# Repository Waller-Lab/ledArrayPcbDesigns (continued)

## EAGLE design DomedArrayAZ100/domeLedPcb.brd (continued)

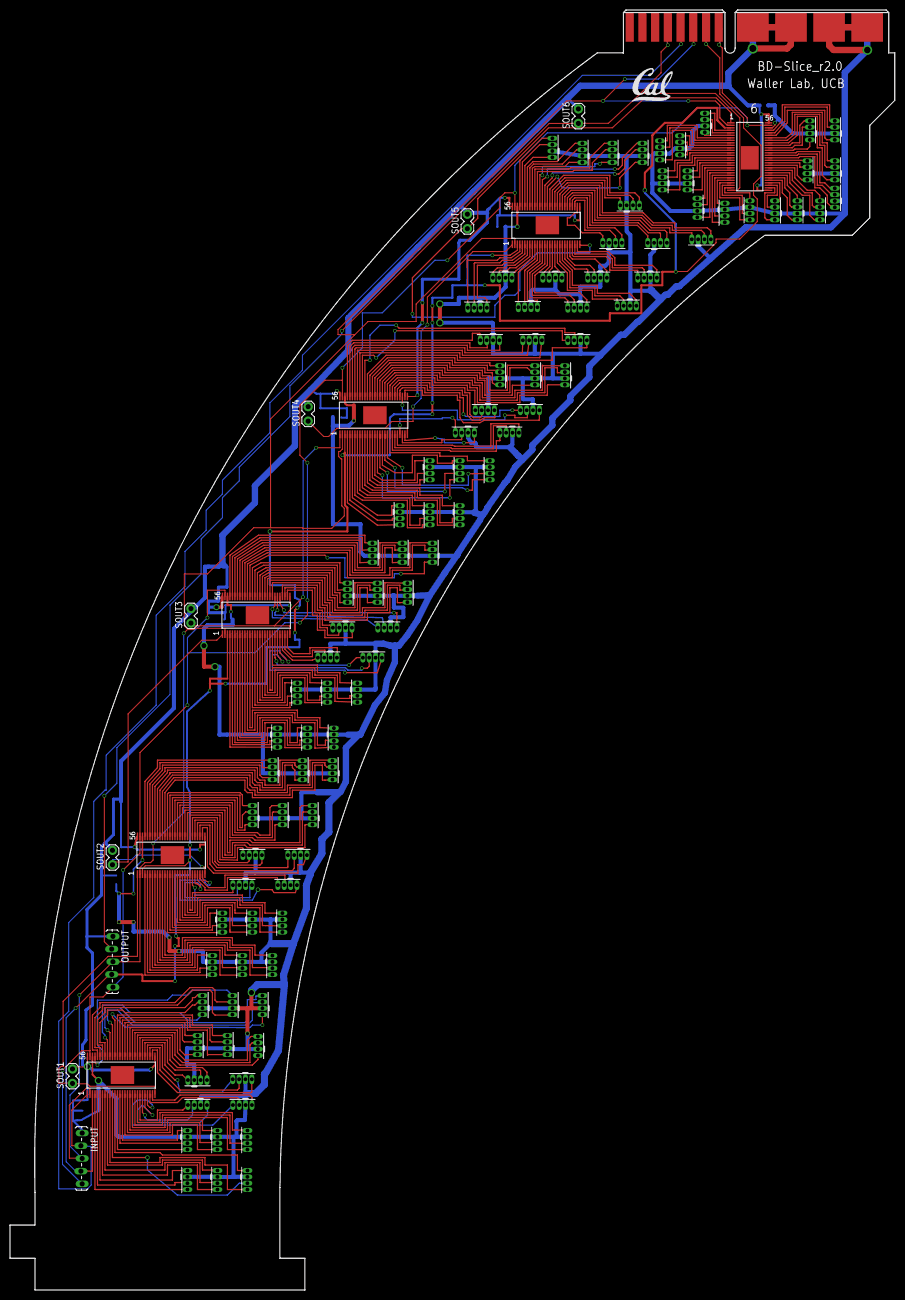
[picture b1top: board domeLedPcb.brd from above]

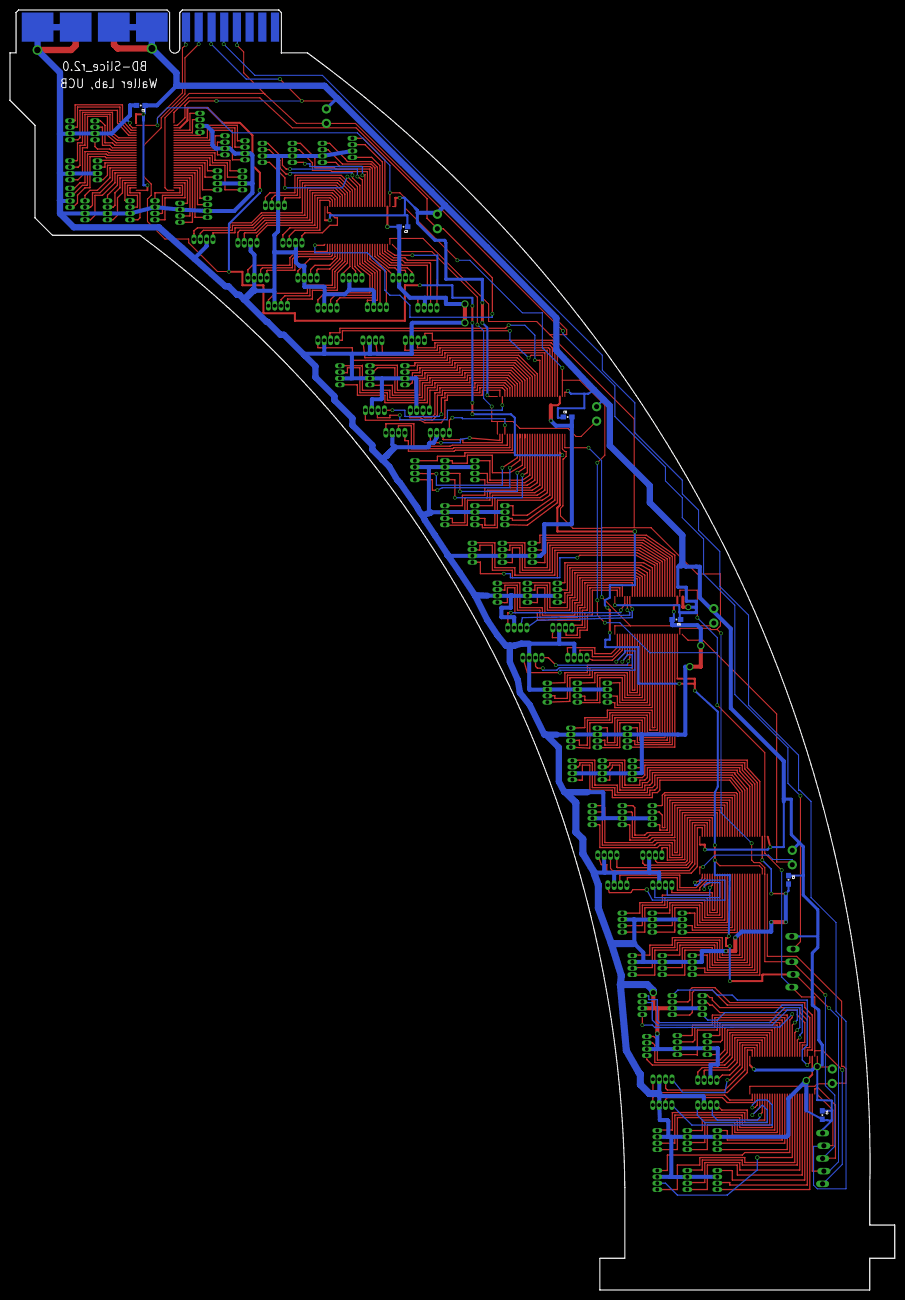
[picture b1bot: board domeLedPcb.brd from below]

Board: 2 copper layers, 177.0 x 256.1 mm, 117 parts (6 on the bottom side), 300 nets.

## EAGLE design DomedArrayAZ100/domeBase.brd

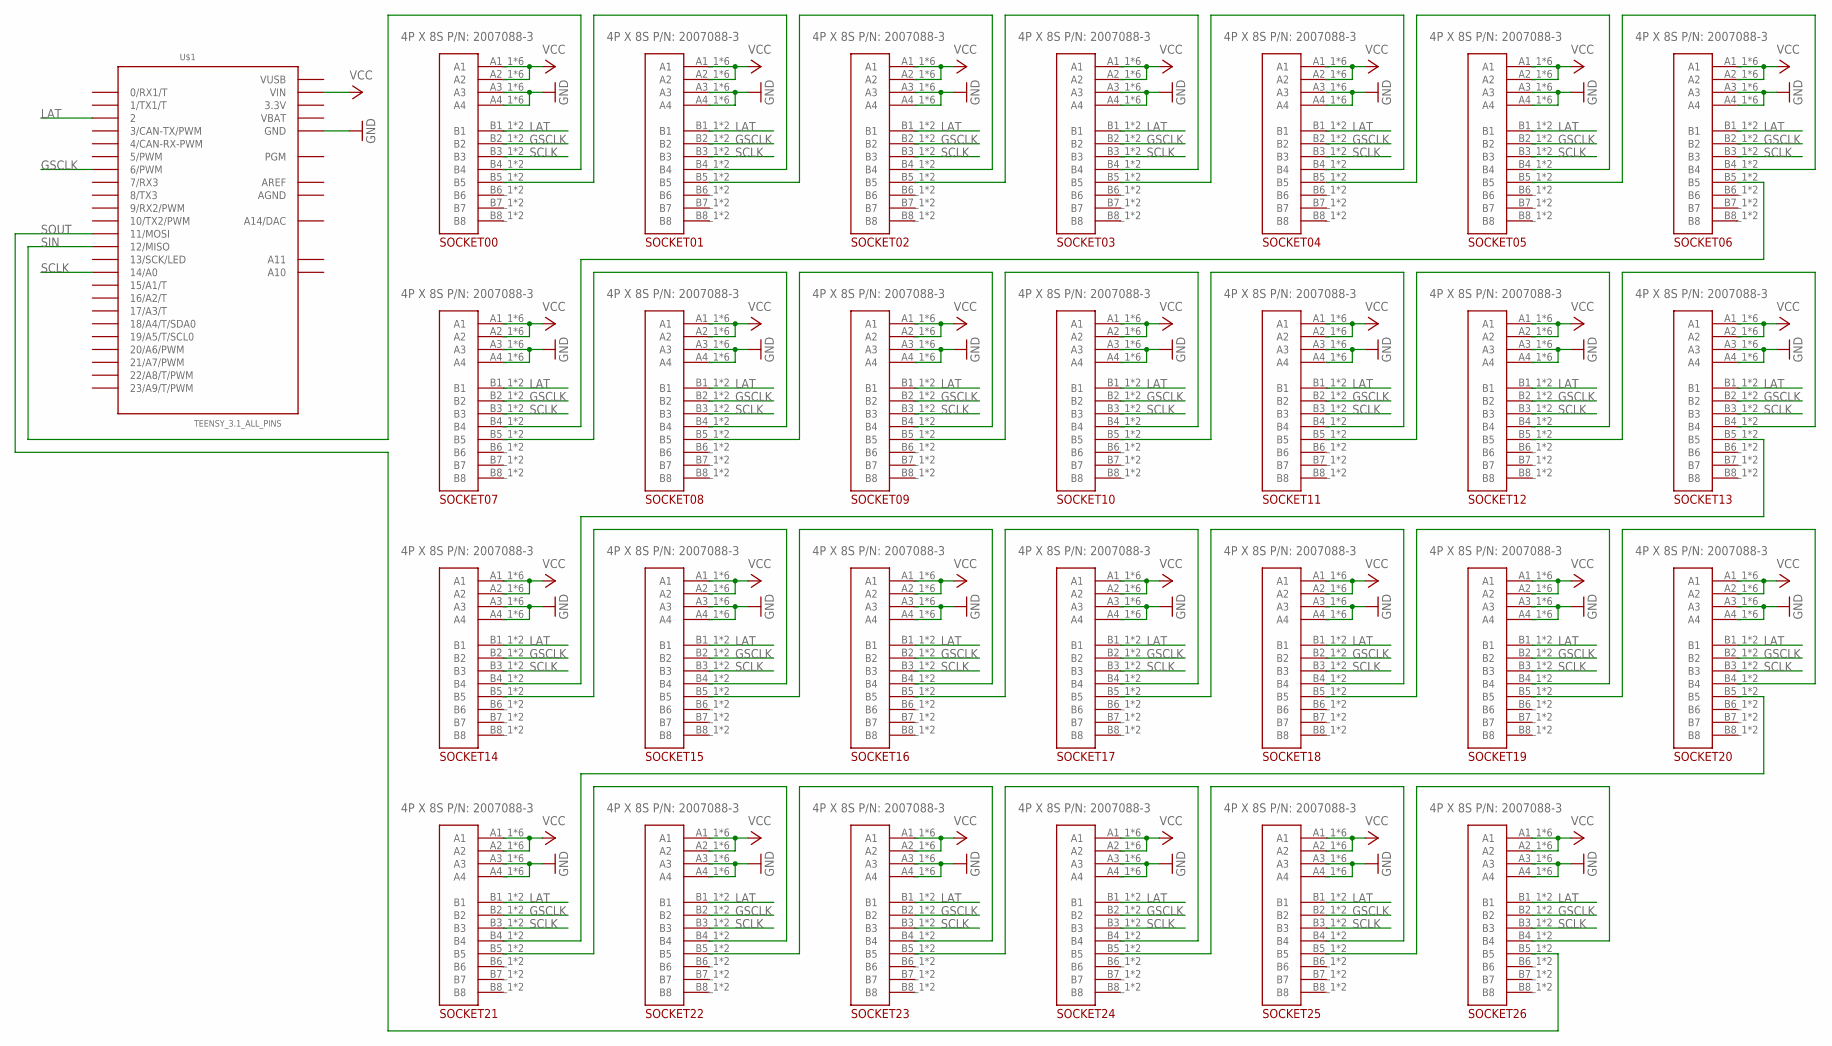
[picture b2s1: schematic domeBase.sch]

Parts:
SOCKET00, SOCKET01, SOCKET02, SOCKET03, SOCKET04, SOCKET05, SOCKET06, SOCKET07, SOCKET08, SOCKET09, SOCKET10, SOCKET11, SOCKET12, SOCKET13, SOCKET14, SOCKET15, SOCKET16, SOCKET17, SOCKET18, SOCKET19, SOCKET20, SOCKET21, SOCKET22, SOCKET23, SOCKET24, SOCKET25, SOCKET26: 4POWER_8SIGNALMOUNTING_BOARD; 4POWER_8SIGNAL_MOUNT
U$1: TEENSY_3.1_ALL_PINS; TEENSY3-ALL_PINS

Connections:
3.3V: U$1.3.3V, U$1.3.3V1 (3.3V)
AGND: U$1.AGND
AREF: U$1.AREF
GND: SOCKET00.A3_1 (A3), SOCKET00.A3_2 (A3), SOCKET00.A3_3 (A3), SOCKET00.A3_4 (A3), SOCKET00.A3_5 (A3), SOCKET00.A3_6 (A3), SOCKET00.A4_1 (A4), SOCKET00.A4_2 (A4), SOCKET00.A4_3 (A4), SOCKET00.A4_4 (A4), SOCKET00.A4_5 (A4), SOCKET00.A4_6 (A4), SOCKET01.A3_1 (A3), SOCKET01.A3_2 (A3), SOCKET01.A3_3 (A3), SOCKET01.A3_4 (A3), SOCKET01.A3_5 (A3), SOCKET01.A3_6 (A3), SOCKET01.A4_1 (A4), SOCKET01.A4_2 (A4), SOCKET01.A4_3 (A4), SOCKET01.A4_4 (A4), SOCKET01.A4_5 (A4), SOCKET01.A4_6 (A4), SOCKET02.A3_1 (A3), SOCKET02.A3_2 (A3), SOCKET02.A3_3 (A3), SOCKET02.A3_4 (A3), SOCKET02.A3_5 (A3), SOCKET02.A3_6 (A3), SOCKET02.A4_1 (A4), SOCKET02.A4_2 (A4), SOCKET02.A4_3 (A4), SOCKET02.A4_4 (A4), SOCKET02.A4_5 (A4), SOCKET02.A4_6 (A4), SOCKET03.A3_1 (A3), SOCKET03.A3_2 (A3), SOCKET03.A3_3 (A3), SOCKET03.A3_4 (A3), SOCKET03.A3_5 (A3), SOCKET03.A3_6 (A3), SOCKET03.A4_1 (A4), SOCKET03.A4_2 (A4), SOCKET03.A4_3 (A4), SOCKET03.A4_4 (A4), SOCKET03.A4_5 (A4), SOCKET03.A4_6 (A4), SOCKET04.A3_1 (A3), SOCKET04.A3_2 (A3), SOCKET04.A3_3 (A3), SOCKET04.A3_4 (A3), SOCKET04.A3_5 (A3), SOCKET04.A3_6 (A3), SOCKET04.A4_1 (A4), SOCKET04.A4_2 (A4), SOCKET04.A4_3 (A4), SOCKET04.A4_4 (A4), SOCKET04.A4_5 (A4), SOCKET04.A4_6 (A4), SOCKET05.A3_1 (A3), SOCKET05.A3_2 (A3), SOCKET05.A3_3 (A3), SOCKET05.A3_4 (A3), SOCKET05.A3_5 (A3), SOCKET05.A3_6 (A3), SOCKET05.A4_1 (A4), SOCKET05.A4_2 (A4), SOCKET05.A4_3 (A4), SOCKET05.A4_4 (A4), SOCKET05.A4_5 (A4), SOCKET05.A4_6 (A4), SOCKET06.A3_1 (A3), SOCKET06.A3_2 (A3), SOCKET06.A3_3 (A3), SOCKET06.A3_4 (A3), SOCKET06.A3_5 (A3), SOCKET06.A3_6 (A3), SOCKET06.A4_1 (A4), SOCKET06.A4_2 (A4), SOCKET06.A4_3 (A4), SOCKET06.A4_4 (A4), SOCKET06.A4_5 (A4), SOCKET06.A4_6 (A4), SOCKET07.A3_1 (A3), SOCKET07.A3_2 (A3), SOCKET07.A3_3 (A3), SOCKET07.A3_4 (A3), SOCKET07.A3_5 (A3), SOCKET07.A3_6 (A3), SOCKET07.A4_1 (A4), SOCKET07.A4_2 (A4), SOCKET07.A4_3 (A4), SOCKET07.A4_4 (A4), SOCKET07.A4_5 (A4), SOCKET07.A4_6 (A4), SOCKET08.A3_1 (A3), SOCKET08.A3_2 (A3), SOCKET08.A3_3 (A3), SOCKET08.A3_4 (A3), SOCKET08.A3_5 (A3), SOCKET08.A3_6 (A3), SOCKET08.A4_1 (A4), SOCKET08.A4_2 (A4), SOCKET08.A4_3 (A4), SOCKET08.A4_4 (A4), SOCKET08.A4_5 (A4), SOCKET08.A4_6 (A4), SOCKET09.A3_1 (A3), SOCKET09.A3_2 (A3), SOCKET09.A3_3 (A3), SOCKET09.A3_4 (A3), SOCKET09.A3_5 (A3), SOCKET09.A3_6 (A3), SOCKET09.A4_1 (A4), SOCKET09.A4_2 (A4), SOCKET09.A4_3 (A4), SOCKET09.A4_4 (A4), SOCKET09.A4_5 (A4), SOCKET09.A4_6 (A4), SOCKET10.A3_1 (A3), SOCKET10.A3_2 (A3), SOCKET10.A3_3 (A3), SOCKET10.A3_4 (A3), SOCKET10.A3_5 (A3), SOCKET10.A3_6 (A3), SOCKET10.A4_1 (A4), SOCKET10.A4_2 (A4), SOCKET10.A4_3 (A4), SOCKET10.A4_4 (A4), SOCKET10.A4_5 (A4), SOCKET10.A4_6 (A4), SOCKET11.A3_1 (A3), SOCKET11.A3_2 (A3), SOCKET11.A3_3 (A3), SOCKET11.A3_4 (A3), SOCKET11.A3_5 (A3), SOCKET11.A3_6 (A3), SOCKET11.A4_1 (A4), SOCKET11.A4_2 (A4), SOCKET11.A4_3 (A4), SOCKET11.A4_4 (A4), SOCKET11.A4_5 (A4), SOCKET11.A4_6 (A4), SOCKET12.A3_1 (A3), SOCKET12.A3_2 (A3), SOCKET12.A3_3 (A3), SOCKET12.A3_4 (A3), SOCKET12.A3_5 (A3), SOCKET12.A3_6 (A3), SOCKET12.A4_1 (A4), SOCKET12.A4_2 (A4), SOCKET12.A4_3 (A4), SOCKET12.A4_4 (A4), SOCKET12.A4_5 (A4), SOCKET12.A4_6 (A4), SOCKET13.A3_1 (A3), SOCKET13.A3_2 (A3), SOCKET13.A3_3 (A3), SOCKET13.A3_4 (A3), SOCKET13.A3_5 (A3), SOCKET13.A3_6 (A3), SOCKET13.A4_1 (A4), SOCKET13.A4_2 (A4), SOCKET13.A4_3 (A4), SOCKET13.A4_4 (A4), SOCKET13.A4_5 (A4), SOCKET13.A4_6 (A4), SOCKET14.A3_1 (A3), SOCKET14.A3_2 (A3), SOCKET14.A3_3 (A3), SOCKET14.A3_4 (A3), SOCKET14.A3_5 (A3), SOCKET14.A3_6 (A3), SOCKET14.A4_1 (A4), SOCKET14.A4_2 (A4), SOCKET14.A4_3 (A4), SOCKET14.A4_4 (A4), SOCKET14.A4_5 (A4), SOCKET14.A4_6 (A4), SOCKET15.A3_1 (A3), SOCKET15.A3_2 (A3), SOCKET15.A3_3 (A3), SOCKET15.A3_4 (A3), SOCKET15.A3_5 (A3), SOCKET15.A3_6 (A3), SOCKET15.A4_1 (A4), SOCKET15.A4_2 (A4), SOCKET15.A4_3 (A4), SOCKET15.A4_4 (A4), SOCKET15.A4_5 (A4), SOCKET15.A4_6 (A4), SOCKET16.A3_1 (A3), SOCKET16.A3_2 (A3), SOCKET16.A3_3 (A3), SOCKET16.A3_4 (A3), SOCKET16.A3_5 (A3), SOCKET16.A3_6 (A3), SOCKET16.A4_1 (A4), SOCKET16.A4_2 (A4), SOCKET16.A4_3 (A4), SOCKET16.A4_4 (A4), SOCKET16.A4_5 (A4), SOCKET16.A4_6 (A4), SOCKET17.A3_1 (A3), SOCKET17.A3_2 (A3), SOCKET17.A3_3 (A3), SOCKET17.A3_4 (A3), SOCKET17.A3_5 (A3), SOCKET17.A3_6 (A3), SOCKET17.A4_1 (A4), SOCKET17.A4_2 (A4), SOCKET17.A4_3 (A4), SOCKET17.A4_4 (A4), SOCKET17.A4_5 (A4), SOCKET17.A4_6 (A4), SOCKET18.A3_1 (A3), SOCKET18.A3_2 (A3), SOCKET18.A3_3 (A3), SOCKET18.A3_4 (A3), SOCKET18.A3_5 (A3), SOCKET18.A3_6 (A3), SOCKET18.A4_1 (A4), SOCKET18.A4_2 (A4), SOCKET18.A4_3 (A4), SOCKET18.A4_4 (A4), SOCKET18.A4_5 (A4), SOCKET18.A4_6 (A4), SOCKET19.A3_1 (A3), SOCKET19.A3_2 (A3), SOCKET19.A3_3 (A3), SOCKET19.A3_4 (A3), SOCKET19.A3_5 (A3), SOCKET19.A3_6 (A3), SOCKET19.A4_1 (A4), SOCKET19.A4_2 (A4), SOCKET19.A4_3 (A4), SOCKET19.A4_4 (A4), SOCKET19.A4_5 (A4), SOCKET19.A4_6 (A4), SOCKET20.A3_1 (A3), SOCKET20.A3_2 (A3), SOCKET20.A3_3 (A3), SOCKET20.A3_4 (A3), SOCKET20.A3_5 (A3), SOCKET20.A3_6 (A3), SOCKET20.A4_1 (A4), SOCKET20.A4_2 (A4), SOCKET20.A4_3 (A4), SOCKET20.A4_4 (A4), SOCKET20.A4_5 (A4), SOCKET20.A4_6 (A4), SOCKET21.A3_1 (A3), SOCKET21.A3_2 (A3), SOCKET21.A3_3 (A3), SOCKET21.A3_4 (A3), SOCKET21.A3_5 (A3), SOCKET21.A3_6 (A3), SOCKET21.A4_1 (A4), SOCKET21.A4_2 (A4), SOCKET21.A4_3 (A4), SOCKET21.A4_4 (A4), SOCKET21.A4_5 (A4), SOCKET21.A4_6 (A4), SOCKET22.A3_1 (A3), SOCKET22.A3_2 (A3), SOCKET22.A3_3 (A3), SOCKET22.A3_4 (A3), SOCKET22.A3_5 (A3), SOCKET22.A3_6 (A3), SOCKET22.A4_1 (A4), SOCKET22.A4_2 (A4), SOCKET22.A4_3 (A4), SOCKET22.A4_4 (A4), SOCKET22.A4_5 (A4), SOCKET22.A4_6 (A4), SOCKET23.A3_1 (A3), SOCKET23.A3_2 (A3), SOCKET23.A3_3 (A3), SOCKET23.A3_4 (A3), SOCKET23.A3_5 (A3), SOCKET23.A3_6 (A3), SOCKET23.A4_1 (A4), SOCKET23.A4_2 (A4), SOCKET23.A4_3 (A4), SOCKET23.A4_4 (A4), SOCKET23.A4_5 (A4), SOCKET23.A4_6 (A4), SOCKET24.A3_1 (A3), SOCKET24.A3_2 (A3), SOCKET24.A3_3 (A3), SOCKET24.A3_4 (A3), SOCKET24.A3_5 (A3), SOCKET24.A3_6 (A3), SOCKET24.A4_1 (A4), SOCKET24.A4_2 (A4), SOCKET24.A4_3 (A4), SOCKET24.A4_4 (A4), SOCKET24.A4_5 (A4), SOCKET24.A4_6 (A4), SOCKET25.A3_1 (A3), SOCKET25.A3_2 (A3), SOCKET25.A3_3 (A3), SOCKET25.A3_4 (A3), SOCKET25.A3_5 (A3), SOCKET25.A3_6 (A3), SOCKET25.A4_1 (A4), SOCKET25.A4_2 (A4), SOCKET25.A4_3 (A4), SOCKET25.A4_4 (A4), SOCKET25.A4_5 (A4), SOCKET25.A4_6 (A4), SOCKET26.A3_1 (A3), SOCKET26.A3_2 (A3), SOCKET26.A3_3 (A3), SOCKET26.A3_4 (A3), SOCKET26.A3_5 (A3), SOCKET26.A3_6 (A3), SOCKET26.A4_1 (A4), SOCKET26.A4_2 (A4), SOCKET26.A4_3 (A4), SOCKET26.A4_4 (A4), SOCKET26.A4_5 (A4), SOCKET26.A4_6 (A4), U$1.GND, U$1.GND1 (GND)
GSCLK: SOCKET00.B2_1 (B2), SOCKET00.B2_2 (B2), SOCKET01.B2_1 (B2), SOCKET01.B2_2 (B2), SOCKET02.B2_1 (B2), SOCKET02.B2_2 (B2), SOCKET03.B2_1 (B2), SOCKET03.B2_2 (B2), SOCKET04.B2_1 (B2), SOCKET04.B2_2 (B2), SOCKET05.B2_1 (B2), SOCKET05.B2_2 (B2), SOCKET06.B2_1 (B2), SOCKET06.B2_2 (B2), SOCKET07.B2_1 (B2), SOCKET07.B2_2 (B2), SOCKET08.B2_1 (B2), SOCKET08.B2_2 (B2), SOCKET09.B2_1 (B2), SOCKET09.B2_2 (B2), SOCKET10.B2_1 (B2), SOCKET10.B2_2 (B2), SOCKET11.B2_1 (B2), SOCKET11.B2_2 (B2), SOCKET12.B2_1 (B2), SOCKET12.B2_2 (B2), SOCKET13.B2_1 (B2), SOCKET13.B2_2 (B2), SOCKET14.B2_1 (B2), SOCKET14.B2_2 (B2), SOCKET15.B2_1 (B2), SOCKET15.B2_2 (B2), SOCKET16.B2_1 (B2), SOCKET16.B2_2 (B2), SOCKET17.B2_1 (B2), SOCKET17.B2_2 (B2), SOCKET18.B2_1 (B2), SOCKET18.B2_2 (B2), SOCKET19.B2_1 (B2), SOCKET19.B2_2 (B2), SOCKET20.B2_1 (B2), SOCKET20.B2_2 (B2), SOCKET21.B2_1 (B2), SOCKET21.B2_2 (B2), SOCKET22.B2_1 (B2), SOCKET22.B2_2 (B2), SOCKET23.B2_1 (B2), SOCKET23.B2_2 (B2), SOCKET24.B2_1 (B2), SOCKET24.B2_2 (B2), SOCKET25.B2_1 (B2), SOCKET25.B2_2 (B2), SOCKET26.B2_1 (B2), SOCKET26.B2_2 (B2), U$1.6 (6/PWM)
LAT: SOCKET00.B1_1 (B1), SOCKET00.B1_2 (B1), SOCKET01.B1_1 (B1), SOCKET01.B1_2 (B1), SOCKET02.B1_1 (B1), SOCKET02.B1_2 (B1), SOCKET03.B1_1 (B1), SOCKET03.B1_2 (B1), SOCKET04.B1_1 (B1), SOCKET04.B1_2 (B1), SOCKET05.B1_1 (B1), SOCKET05.B1_2 (B1), SOCKET06.B1_1 (B1), SOCKET06.B1_2 (B1), SOCKET07.B1_1 (B1), SOCKET07.B1_2 (B1), SOCKET08.B1_1 (B1), SOCKET08.B1_2 (B1), SOCKET09.B1_1 (B1), SOCKET09.B1_2 (B1), SOCKET10.B1_1 (B1), SOCKET10.B1_2 (B1), SOCKET11.B1_1 (B1), SOCKET11.B1_2 (B1), SOCKET12.B1_1 (B1), SOCKET12.B1_2 (B1), SOCKET13.B1_1 (B1), SOCKET13.B1_2 (B1), SOCKET14.B1_1 (B1), SOCKET14.B1_2 (B1), SOCKET15.B1_1 (B1), SOCKET15.B1_2 (B1), SOCKET16.B1_1 (B1), SOCKET16.B1_2 (B1), SOCKET17.B1_1 (B1), SOCKET17.B1_2 (B1), SOCKET18.B1_1 (B1), SOCKET18.B1_2 (B1), SOCKET19.B1_1 (B1), SOCKET19.B1_2 (B1), SOCKET20.B1_1 (B1), SOCKET20.B1_2 (B1), SOCKET21.B1_1 (B1), SOCKET21.B1_2 (B1), SOCKET22.B1_1 (B1), SOCKET22.B1_2 (B1), SOCKET23.B1_1 (B1), SOCKET23.B1_2 (B1), SOCKET24.B1_1 (B1), SOCKET24.B1_2 (B1), SOCKET25.B1_1 (B1), SOCKET25.B1_2 (B1), SOCKET26.B1_1 (B1), SOCKET26.B1_2 (B1), U$1.2
unnamed: SOCKET00.B5_1 (B5), SOCKET00.B5_2 (B5), SOCKET01.B4_1 (B4), SOCKET01.B4_2 (B4)
unnamed: SOCKET01.B5_1 (B5), SOCKET01.B5_2 (B5), SOCKET02.B4_1 (B4), SOCKET02.B4_2 (B4)
unnamed: SOCKET02.B5_1 (B5), SOCKET02.B5_2 (B5), SOCKET03.B4_1 (B4), SOCKET03.B4_2 (B4)
unnamed: SOCKET03.B5_1 (B5), SOCKET03.B5_2 (B5), SOCKET04.B4_1 (B4), SOCKET04.B4_2 (B4)
unnamed: SOCKET04.B5_1 (B5), SOCKET04.B5_2 (B5), SOCKET05.B4_1 (B4), SOCKET05.B4_2 (B4)
unnamed: SOCKET05.B5_1 (B5), SOCKET05.B5_2 (B5), SOCKET06.B4_1 (B4), SOCKET06.B4_2 (B4)
unnamed: SOCKET06.B5_1 (B5), SOCKET06.B5_2 (B5), SOCKET07.B4_1 (B4), SOCKET07.B4_2 (B4)
unnamed: SOCKET07.B5_1 (B5), SOCKET07.B5_2 (B5), SOCKET08.B4_1 (B4), SOCKET08.B4_2 (B4)
unnamed: SOCKET08.B5_1 (B5), SOCKET08.B5_2 (B5), SOCKET09.B4_1 (B4), SOCKET09.B4_2 (B4)
unnamed: SOCKET09.B5_1 (B5), SOCKET09.B5_2 (B5), SOCKET10.B4_1 (B4), SOCKET10.B4_2 (B4)
unnamed: SOCKET10.B5_1 (B5), SOCKET10.B5_2 (B5), SOCKET11.B4_1 (B4), SOCKET11.B4_2 (B4)
unnamed: SOCKET11.B5_1 (B5), SOCKET11.B5_2 (B5), SOCKET12.B4_1 (B4), SOCKET12.B4_2 (B4)
unnamed: SOCKET12.B5_1 (B5), SOCKET12.B5_2 (B5), SOCKET13.B4_1 (B4), SOCKET13.B4_2 (B4)
unnamed: SOCKET13.B5_1 (B5), SOCKET13.B5_2 (B5), SOCKET14.B4_1 (B4), SOCKET14.B4_2 (B4)
unnamed: SOCKET14.B5_1 (B5), SOCKET14.B5_2 (B5), SOCKET15.B4_1 (B4), SOCKET15.B4_2 (B4)
unnamed: SOCKET15.B5_1 (B5), SOCKET15.B5_2 (B5), SOCKET16.B4_1 (B4), SOCKET16.B4_2 (B4)
unnamed: SOCKET16.B5_1 (B5), SOCKET16.B5_2 (B5), SOCKET17.B4_1 (B4), SOCKET17.B4_2 (B4)
unnamed: SOCKET17.B5_1 (B5), SOCKET17.B5_2 (B5), SOCKET18.B4_1 (B4), SOCKET18.B4_2 (B4)
unnamed: SOCKET18.B5_1 (B5), SOCKET18.B5_2 (B5), SOCKET19.B4_1 (B4), SOCKET19.B4_2 (B4)
unnamed: SOCKET19.B5_1 (B5), SOCKET19.B5_2 (B5), SOCKET20.B4_1 (B4), SOCKET20.B4_2 (B4)
unnamed: SOCKET20.B5_1 (B5), SOCKET20.B5_2 (B5), SOCKET21.B4_1 (B4), SOCKET21.B4_2 (B4)
unnamed: SOCKET21.B5_1 (B5), SOCKET21.B5_2 (B5), SOCKET22.B4_1 (B4), SOCKET22.B4_2 (B4)
unnamed: SOCKET22.B5_1 (B5), SOCKET22.B5_2 (B5), SOCKET23.B4_1 (B4), SOCKET23.B4_2 (B4)
unnamed: SOCKET23.B5_1 (B5), SOCKET23.B5_2 (B5), SOCKET24.B4_1 (B4), SOCKET24.B4_2 (B4)
unnamed: SOCKET24.B5_1 (B5), SOCKET24.B5_2 (B5), SOCKET25.B4_1 (B4), SOCKET25.B4_2 (B4)
unnamed: SOCKET25.B5_1 (B5), SOCKET25.B5_2 (B5), SOCKET26.B4_1 (B4), SOCKET26.B4_2 (B4)
SCLK: SOCKET00.B3_1 (B3), SOCKET00.B3_2 (B3), SOCKET01.B3_1 (B3), SOCKET01.B3_2 (B3), SOCKET02.B3_1 (B3), SOCKET02.B3_2 (B3), SOCKET03.B3_1 (B3), SOCKET03.B3_2 (B3), SOCKET04.B3_1 (B3), SOCKET04.B3_2 (B3), SOCKET05.B3_1 (B3), SOCKET05.B3_2 (B3), SOCKET06.B3_1 (B3), SOCKET06.B3_2 (B3), SOCKET07.B3_1 (B3), SOCKET07.B3_2 (B3), SOCKET08.B3_1 (B3), SOCKET08.B3_2 (B3), SOCKET09.B3_1 (B3), SOCKET09.B3_2 (B3), SOCKET10.B3_1 (B3), SOCKET10.B3_2 (B3), SOCKET11.B3_1 (B3), SOCKET11.B3_2 (B3), SOCKET12.B3_1 (B3), SOCKET12.B3_2 (B3), SOCKET13.B3_1 (B3), SOCKET13.B3_2 (B3), SOCKET14.B3_1 (B3), SOCKET14.B3_2 (B3), SOCKET15.B3_1 (B3), SOCKET15.B3_2 (B3), SOCKET16.B3_1 (B3), SOCKET16.B3_2 (B3), SOCKET17.B3_1 (B3), SOCKET17.B3_2 (B3), SOCKET18.B3_1 (B3), SOCKET18.B3_2 (B3), SOCKET19.B3_1 (B3), SOCKET19.B3_2 (B3), SOCKET20.B3_1 (B3), SOCKET20.B3_2 (B3), SOCKET21.B3_1 (B3), SOCKET21.B3_2 (B3), SOCKET22.B3_1 (B3), SOCKET22.B3_2 (B3), SOCKET23.B3_1 (B3), SOCKET23.B3_2 (B3), SOCKET24.B3_1 (B3), SOCKET24.B3_2 (B3), SOCKET25.B3_1 (B3), SOCKET25.B3_2 (B3), SOCKET26.B3_1 (B3), SOCKET26.B3_2 (B3), U$1.14/A0
SIN: SOCKET00.B4_1 (B4), SOCKET00.B4_2 (B4), U$1.12 (12/MISO)
SOUT: SOCKET26.B5_1 (B5), SOCKET26.B5_2 (B5), U$1.11 (11/MOSI)
VBAT: U$1.VBAT
VCC: SOCKET00.A1_1 (A1), SOCKET00.A1_2 (A1), SOCKET00.A1_3 (A1), SOCKET00.A1_4 (A1), SOCKET00.A1_5 (A1), SOCKET00.A1_6 (A1), SOCKET00.A2_1 (A2), SOCKET00.A2_2 (A2), SOCKET00.A2_3 (A2), SOCKET00.A2_4 (A2), SOCKET00.A2_5 (A2), SOCKET00.A2_6 (A2), SOCKET01.A1_1 (A1), SOCKET01.A1_2 (A1), SOCKET01.A1_3 (A1), SOCKET01.A1_4 (A1), SOCKET01.A1_5 (A1), SOCKET01.A1_6 (A1), SOCKET01.A2_1 (A2), SOCKET01.A2_2 (A2), SOCKET01.A2_3 (A2), SOCKET01.A2_4 (A2), SOCKET01.A2_5 (A2), SOCKET01.A2_6 (A2), SOCKET02.A1_1 (A1), SOCKET02.A1_2 (A1), SOCKET02.A1_3 (A1), SOCKET02.A1_4 (A1), SOCKET02.A1_5 (A1), SOCKET02.A1_6 (A1), SOCKET02.A2_1 (A2), SOCKET02.A2_2 (A2), SOCKET02.A2_3 (A2), SOCKET02.A2_4 (A2), SOCKET02.A2_5 (A2), SOCKET02.A2_6 (A2), SOCKET03.A1_1 (A1), SOCKET03.A1_2 (A1), SOCKET03.A1_3 (A1), SOCKET03.A1_4 (A1), SOCKET03.A1_5 (A1), SOCKET03.A1_6 (A1), SOCKET03.A2_1 (A2), SOCKET03.A2_2 (A2), SOCKET03.A2_3 (A2), SOCKET03.A2_4 (A2), SOCKET03.A2_5 (A2), SOCKET03.A2_6 (A2), SOCKET04.A1_1 (A1), SOCKET04.A1_2 (A1), SOCKET04.A1_3 (A1), SOCKET04.A1_4 (A1), SOCKET04.A1_5 (A1), SOCKET04.A1_6 (A1), SOCKET04.A2_1 (A2), SOCKET04.A2_2 (A2), SOCKET04.A2_3 (A2), SOCKET04.A2_4 (A2), SOCKET04.A2_5 (A2), SOCKET04.A2_6 (A2), SOCKET05.A1_1 (A1), SOCKET05.A1_2 (A1), SOCKET05.A1_3 (A1), SOCKET05.A1_4 (A1), SOCKET05.A1_5 (A1), SOCKET05.A1_6 (A1), SOCKET05.A2_1 (A2), SOCKET05.A2_2 (A2), SOCKET05.A2_3 (A2), SOCKET05.A2_4 (A2), SOCKET05.A2_5 (A2), SOCKET05.A2_6 (A2), SOCKET06.A1_1 (A1), SOCKET06.A1_2 (A1), SOCKET06.A1_3 (A1), SOCKET06.A1_4 (A1), SOCKET06.A1_5 (A1), SOCKET06.A1_6 (A1), SOCKET06.A2_1 (A2), SOCKET06.A2_2 (A2), SOCKET06.A2_3 (A2), SOCKET06.A2_4 (A2), SOCKET06.A2_5 (A2), SOCKET06.A2_6 (A2), SOCKET07.A1_1 (A1), SOCKET07.A1_2 (A1), SOCKET07.A1_3 (A1), SOCKET07.A1_4 (A1), SOCKET07.A1_5 (A1), SOCKET07.A1_6 (A1), SOCKET07.A2_1 (A2), SOCKET07.A2_2 (A2), SOCKET07.A2_3 (A2), SOCKET07.A2_4 (A2), SOCKET07.A2_5 (A2), SOCKET07.A2_6 (A2), SOCKET08.A1_1 (A1), SOCKET08.A1_2 (A1), SOCKET08.A1_3 (A1), SOCKET08.A1_4 (A1), SOCKET08.A1_5 (A1), SOCKET08.A1_6 (A1), SOCKET08.A2_1 (A2), SOCKET08.A2_2 (A2), SOCKET08.A2_3 (A2), SOCKET08.A2_4 (A2), SOCKET08.A2_5 (A2), SOCKET08.A2_6 (A2), SOCKET09.A1_1 (A1), SOCKET09.A1_2 (A1), SOCKET09.A1_3 (A1), SOCKET09.A1_4 (A1), SOCKET09.A1_5 (A1), SOCKET09.A1_6 (A1), SOCKET09.A2_1 (A2), SOCKET09.A2_2 (A2), SOCKET09.A2_3 (A2), SOCKET09.A2_4 (A2), SOCKET09.A2_5 (A2), SOCKET09.A2_6 (A2), SOCKET10.A1_1 (A1), SOCKET10.A1_2 (A1), SOCKET10.A1_3 (A1), SOCKET10.A1_4 (A1), SOCKET10.A1_5 (A1), SOCKET10.A1_6 (A1), SOCKET10.A2_1 (A2), SOCKET10.A2_2 (A2), SOCKET10.A2_3 (A2), SOCKET10.A2_4 (A2), SOCKET10.A2_5 (A2), SOCKET10.A2_6 (A2), SOCKET11.A1_1 (A1), SOCKET11.A1_2 (A1), SOCKET11.A1_3 (A1), SOCKET11.A1_4 (A1), SOCKET11.A1_5 (A1), SOCKET11.A1_6 (A1), SOCKET11.A2_1 (A2), SOCKET11.A2_2 (A2), SOCKET11.A2_3 (A2), SOCKET11.A2_4 (A2), SOCKET11.A2_5 (A2), SOCKET11.A2_6 (A2), SOCKET12.A1_1 (A1), SOCKET12.A1_2 (A1), SOCKET12.A1_3 (A1), SOCKET12.A1_4 (A1), SOCKET12.A1_5 (A1), SOCKET12.A1_6 (A1), SOCKET12.A2_1 (A2), SOCKET12.A2_2 (A2), SOCKET12.A2_3 (A2), SOCKET12.A2_4 (A2), SOCKET12.A2_5 (A2), SOCKET12.A2_6 (A2), SOCKET13.A1_1 (A1), SOCKET13.A1_2 (A1), SOCKET13.A1_3 (A1), SOCKET13.A1_4 (A1), SOCKET13.A1_5 (A1), SOCKET13.A1_6 (A1), SOCKET13.A2_1 (A2), SOCKET13.A2_2 (A2), SOCKET13.A2_3 (A2), SOCKET13.A2_4 (A2), SOCKET13.A2_5 (A2), SOCKET13.A2_6 (A2), SOCKET14.A1_1 (A1), SOCKET14.A1_2 (A1), SOCKET14.A1_3 (A1), SOCKET14.A1_4 (A1), SOCKET14.A1_5 (A1), SOCKET14.A1_6 (A1), SOCKET14.A2_1 (A2), SOCKET14.A2_2 (A2), SOCKET14.A2_3 (A2), SOCKET14.A2_4 (A2), SOCKET14.A2_5 (A2), SOCKET14.A2_6 (A2), SOCKET15.A1_1 (A1), SOCKET15.A1_2 (A1), SOCKET15.A1_3 (A1), SOCKET15.A1_4 (A1), SOCKET15.A1_5 (A1), SOCKET15.A1_6 (A1), SOCKET15.A2_1 (A2), SOCKET15.A2_2 (A2), SOCKET15.A2_3 (A2), SOCKET15.A2_4 (A2), SOCKET15.A2_5 (A2), SOCKET15.A2_6 (A2), SOCKET16.A1_1 (A1), SOCKET16.A1_2 (A1), SOCKET16.A1_3 (A1), SOCKET16.A1_4 (A1), SOCKET16.A1_5 (A1), SOCKET16.A1_6 (A1), SOCKET16.A2_1 (A2), SOCKET16.A2_2 (A2), SOCKET16.A2_3 (A2), SOCKET16.A2_4 (A2), SOCKET16.A2_5 (A2), SOCKET16.A2_6 (A2), SOCKET17.A1_1 (A1), SOCKET17.A1_2 (A1), SOCKET17.A1_3 (A1), SOCKET17.A1_4 (A1), SOCKET17.A1_5 (A1), SOCKET17.A1_6 (A1), SOCKET17.A2_1 (A2), SOCKET17.A2_2 (A2), SOCKET17.A2_3 (A2), SOCKET17.A2_4 (A2), SOCKET17.A2_5 (A2), SOCKET17.A2_6 (A2), SOCKET18.A1_1 (A1), SOCKET18.A1_2 (A1), SOCKET18.A1_3 (A1), SOCKET18.A1_4 (A1), SOCKET18.A1_5 (A1), SOCKET18.A1_6 (A1), SOCKET18.A2_1 (A2), SOCKET18.A2_2 (A2), SOCKET18.A2_3 (A2), SOCKET18.A2_4 (A2), SOCKET18.A2_5 (A2), SOCKET18.A2_6 (A2), SOCKET19.A1_1 (A1), SOCKET19.A1_2 (A1), SOCKET19.A1_3 (A1), SOCKET19.A1_4 (A1), SOCKET19.A1_5 (A1), SOCKET19.A1_6 (A1), SOCKET19.A2_1 (A2), SOCKET19.A2_2 (A2), SOCKET19.A2_3 (A2), SOCKET19.A2_4 (A2), SOCKET19.A2_5 (A2), SOCKET19.A2_6 (A2), SOCKET20.A1_1 (A1), SOCKET20.A1_2 (A1), SOCKET20.A1_3 (A1), SOCKET20.A1_4 (A1), SOCKET20.A1_5 (A1), SOCKET20.A1_6 (A1), SOCKET20.A2_1 (A2), SOCKET20.A2_2 (A2), SOCKET20.A2_3 (A2), SOCKET20.A2_4 (A2), SOCKET20.A2_5 (A2), SOCKET20.A2_6 (A2), SOCKET21.A1_1 (A1), SOCKET21.A1_2 (A1), SOCKET21.A1_3 (A1), SOCKET21.A1_4 (A1), SOCKET21.A1_5 (A1), SOCKET21.A1_6 (A1), SOCKET21.A2_1 (A2), SOCKET21.A2_2 (A2), SOCKET21.A2_3 (A2), SOCKET21.A2_4 (A2), SOCKET21.A2_5 (A2), SOCKET21.A2_6 (A2), SOCKET22.A1_1 (A1), SOCKET22.A1_2 (A1), SOCKET22.A1_3 (A1), SOCKET22.A1_4 (A1), SOCKET22.A1_5 (A1), SOCKET22.A1_6 (A1), SOCKET22.A2_1 (A2), SOCKET22.A2_2 (A2), SOCKET22.A2_3 (A2), SOCKET22.A2_4 (A2), SOCKET22.A2_5 (A2), SOCKET22.A2_6 (A2), SOCKET23.A1_1 (A1), SOCKET23.A1_2 (A1), SOCKET23.A1_3 (A1), SOCKET23.A1_4 (A1), SOCKET23.A1_5 (A1), SOCKET23.A1_6 (A1), SOCKET23.A2_1 (A2), SOCKET23.A2_2 (A2), SOCKET23.A2_3 (A2), SOCKET23.A2_4 (A2), SOCKET23.A2_5 (A2), SOCKET23.A2_6 (A2), SOCKET24.A1_1 (A1), SOCKET24.A1_2 (A1), SOCKET24.A1_3 (A1), SOCKET24.A1_4 (A1), SOCKET24.A1_5 (A1), SOCKET24.A1_6 (A1), SOCKET24.A2_1 (A2), SOCKET24.A2_2 (A2), SOCKET24.A2_3 (A2), SOCKET24.A2_4 (A2), SOCKET24.A2_5 (A2), SOCKET24.A2_6 (A2), SOCKET25.A1_1 (A1), SOCKET25.A1_2 (A1), SOCKET25.A1_3 (A1), SOCKET25.A1_4 (A1), SOCKET25.A1_5 (A1), SOCKET25.A1_6 (A1), SOCKET25.A2_1 (A2), SOCKET25.A2_2 (A2), SOCKET25.A2_3 (A2), SOCKET25.A2_4 (A2), SOCKET25.A2_5 (A2), SOCKET25.A2_6 (A2), SOCKET26.A1_1 (A1), SOCKET26.A1_2 (A1), SOCKET26.A1_3 (A1), SOCKET26.A1_4 (A1), SOCKET26.A1_5 (A1), SOCKET26.A1_6 (A1), SOCKET26.A2_1 (A2), SOCKET26.A2_2 (A2), SOCKET26.A2_3 (A2), SOCKET26.A2_4 (A2), SOCKET26.A2_5 (A2), SOCKET26.A2_6 (A2), U$1.VIN
VUSB: U$1.VUSB

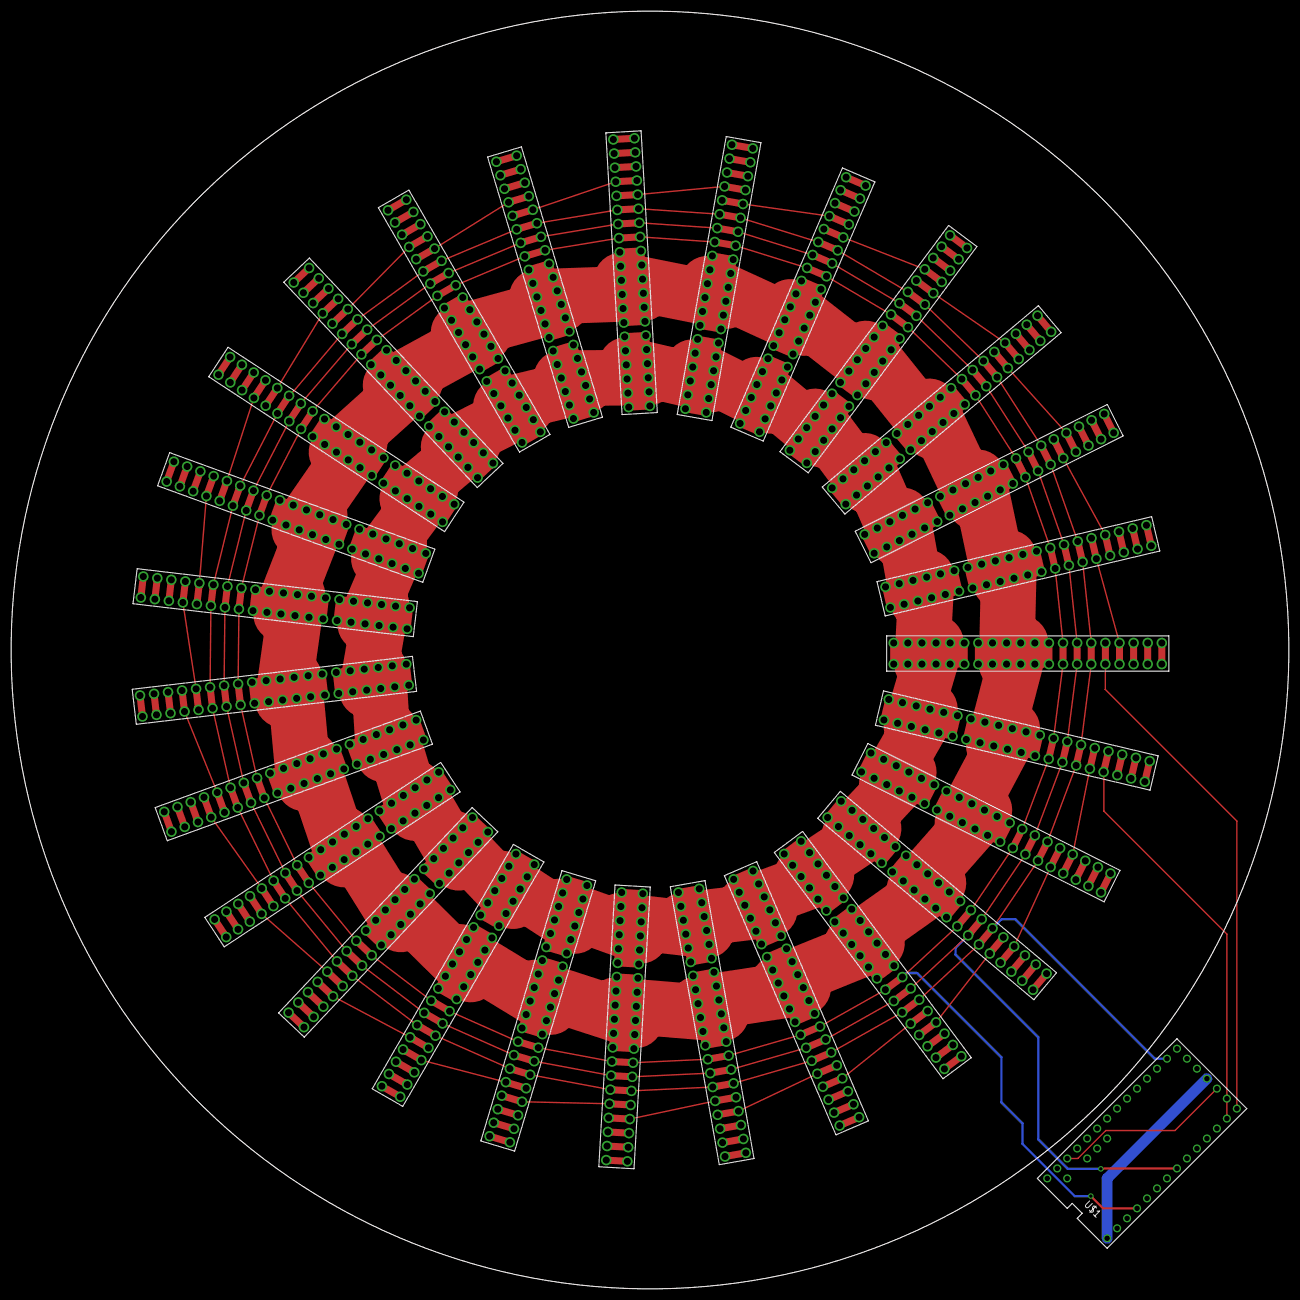
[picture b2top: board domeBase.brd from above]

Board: 2 copper layers, 230.0 x 230.0 mm, 28 parts (0 on the bottom side), 34 nets.
